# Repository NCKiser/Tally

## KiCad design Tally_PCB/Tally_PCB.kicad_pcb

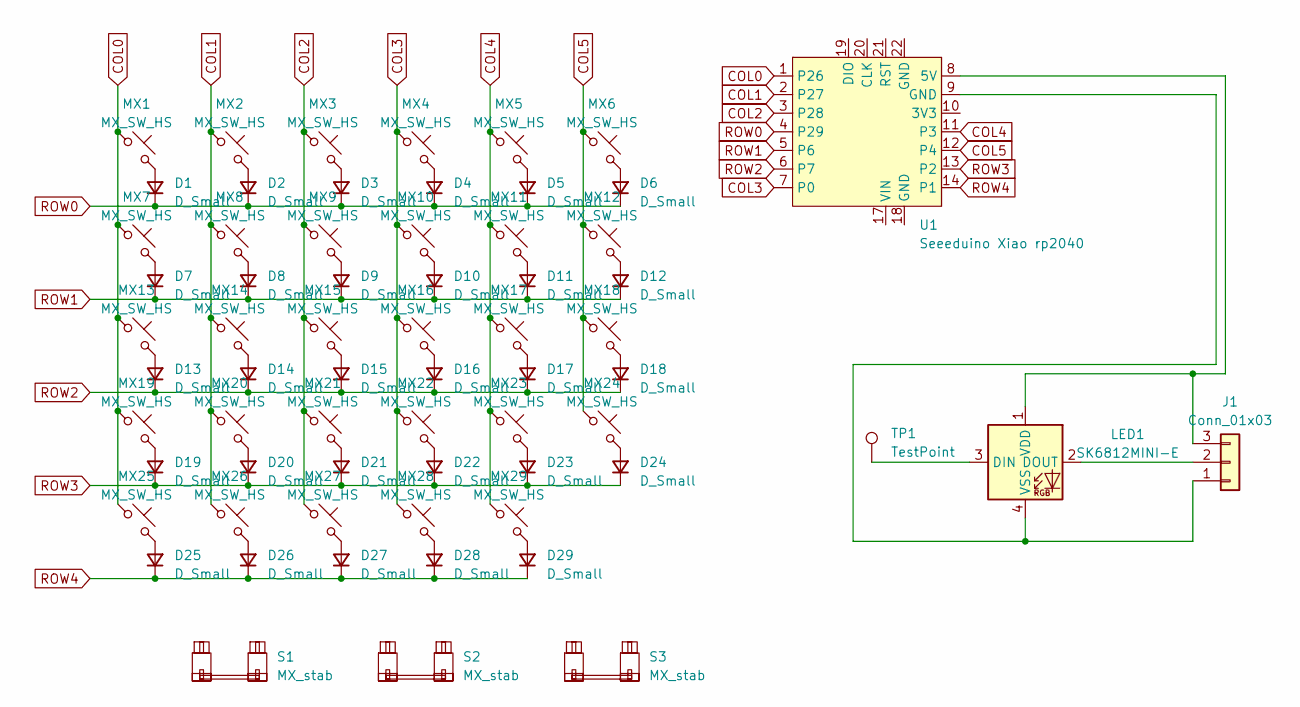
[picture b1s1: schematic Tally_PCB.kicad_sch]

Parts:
D1, D2, D3, D4, D5, D6, D7, D8, D9, D10, D11, D12, D13, D14, D15, D16, D17, D18, D19, D20, D21, D22, D23, D24, D25, D26, D27, D28, D29: D_Small; D_SOD-123
J1: Conn_01x03; PinHeader_1x03_P2.54mm_Vertical
LED1: SK6812MINI-E; LED_MX_6028R
MX1: MX_SW_HS; SW_MX_HS_1.5u
MX2, MX3, MX4, MX5, MX6, MX8, MX9, MX10, MX11, MX12, MX13, MX14, MX15, MX16, MX17, MX18, MX20, MX21, MX22, MX23, MX24, MX25, MX26, MX27, MX28, MX29: MX_SW_HS; SW_MX_HS_1u
MX7: MX_SW_HS; SW_MX_HS_1.75u_STP_1.25
MX19: MX_SW_HS; SW_MX_HS_1.25u
S1: MX_stab; STAB_MX_P_2u
S2: MX_stab; STAB_MX_P_2.75u
S3: MX_stab; STAB_MX_P_ISO-ROT
TP1: TestPoint; TestPoint_THTPad_D2.0mm_Drill1.0mm
U1: Seeeduino Xiao rp2040; Xiao_rp2040_ACH

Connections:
COL0: MX1.1, MX7.1, MX13.1, MX19.1, MX25.1, U1.1 (P26)
COL1: MX2.1, MX8.1, MX14.1, MX20.1, MX26.1, U1.2 (P27)
COL2: MX3.1, MX9.1, MX15.1, MX21.1, MX27.1, U1.3 (P28)
COL3: MX4.1, MX10.1, MX16.1, MX22.1, MX28.1, U1.7 (P0)
COL4: MX5.1, MX11.1, MX17.1, MX23.1, MX29.1, U1.11 (P3)
COL5: MX6.1, MX12.1, MX18.1, MX24.1, U1.12 (P4)
unnamed: D1.2 (A), MX1.2
unnamed: D2.2 (A), MX2.2
unnamed: D3.2 (A), MX3.2
unnamed: D4.2 (A), MX4.2
unnamed: D5.2 (A), MX5.2
unnamed: D6.2 (A), MX6.2
unnamed: D7.2 (A), MX7.2
unnamed: D8.2 (A), MX8.2
unnamed: D9.2 (A), MX9.2
unnamed: D10.2 (A), MX10.2
unnamed: D11.2 (A), MX11.2
unnamed: D12.2 (A), MX12.2
unnamed: D13.2 (A), MX13.2
unnamed: D14.2 (A), MX14.2
unnamed: D15.2 (A), MX15.2
unnamed: D16.2 (A), MX16.2
unnamed: D17.2 (A), MX17.2
unnamed: D18.2 (A), MX18.2
unnamed: D19.2 (A), MX19.2
unnamed: D20.2 (A), MX20.2
unnamed: D21.2 (A), MX21.2
unnamed: D22.2 (A), MX22.2
unnamed: D23.2 (A), MX23.2
unnamed: D24.2 (A), MX24.2
unnamed: D25.2 (A), MX25.2
unnamed: D26.2 (A), MX26.2
unnamed: D27.2 (A), MX27.2
unnamed: D28.2 (A), MX28.2
unnamed: D29.2 (A), MX29.2
unnamed: J1.1, LED1.4 (VSS), U1.9 (GND)
unnamed: J1.2, LED1.2 (DOUT)
unnamed: J1.3, LED1.1 (VDD), U1.8 (5V)
unnamed: LED1.3 (DIN), TP1.1
ROW0: D1.1 (K), D2.1 (K), D3.1 (K), D4.1 (K), D5.1 (K), D6.1 (K), U1.4 (P29)
ROW1: D7.1 (K), D8.1 (K), D9.1 (K), D10.1 (K), D11.1 (K), D12.1 (K), U1.5 (P6)
ROW2: D13.1 (K), D14.1 (K), D15.1 (K), D16.1 (K), D17.1 (K), D18.1 (K), U1.6 (P7)
ROW3: D19.1 (K), D20.1 (K), D21.1 (K), D22.1 (K), D23.1 (K), D24.1 (K), U1.13 (P2)
ROW4: D25.1 (K), D26.1 (K), D27.1 (K), D28.1 (K), D29.1 (K), U1.14 (P1)

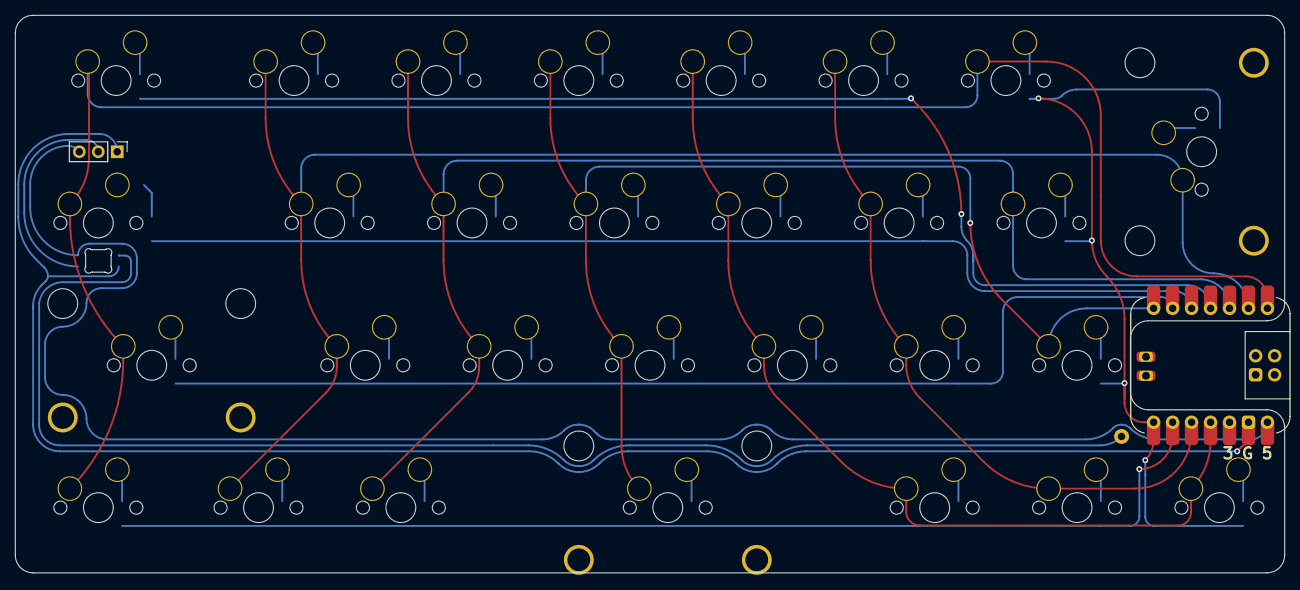
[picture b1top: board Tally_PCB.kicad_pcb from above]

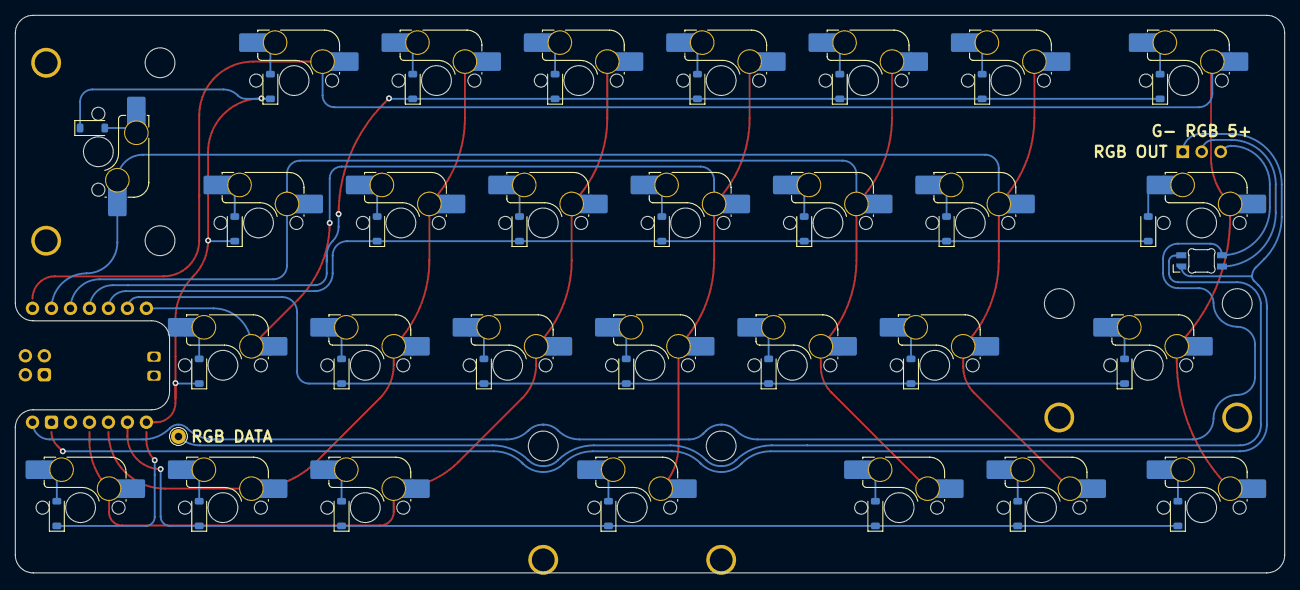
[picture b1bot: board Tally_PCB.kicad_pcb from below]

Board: 2 copper layers, 169.9 x 74.6 mm, 65 parts (60 on the bottom side), 44 nets.

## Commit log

2024-02-07 add .step
